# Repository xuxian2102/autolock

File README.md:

# HomeKey Lock Rev A — PN7161 / ESP32-C6

本工程是面向嘉立创 4 层 PCB + 单面 PCBA 的第一版工程样机，目标是：

1. iPhone / Apple Watch 通过真正的 Apple HomeKey 认证；
2. ESP32-C6 驱动 180° DS3115 舵机压下室内门把手并立即复位；
3. 3S 保护电池供电，USB-C 可单独给逻辑与 NFC 供电、刷机和调试；
4. 门外不增加可见器件，不接门磁、不集成 3S 充电器。

## Rev A 设计边界

- 主控：ESP32-C6-MINI-1-N4，4 MB Flash。
- NFC：PN7161B1HN/C100E，SPI，27.12 MHz 晶振。
- 天线：PCB 顶层 40 mm × 40 mm、4 匝、0.4 mm 线宽、0.3 mm 间距；匹配值按 NXP AN13219 Rev.1.6 的首次迭代值。
- 电池输入：9.0–12.6 V（3S 保护电池或 12 V/5 A 台式适配器）。
- 舵机输出：约 5.94 V，TPS565201 额定 5 A；仅在动作时使能。
- USB-C：USB 2.0 D+/D− 连接 ESP32-C6 原生 USB Serial/JTAG；USB VBUS 只能带逻辑/NFC，不能带舵机。
- USB 与电池逻辑 5 V 用两颗 B5819W 肖特基二极管合路，互不反灌；`SYS_5V` 会比来源低约 0.2–0.4 V。
- 板层：4 层、1.6 mm、1 oz；所有器件位于顶层，降低 PCBA 成本。
- 不含：电池充电、门状态检测、机械限位检测、认证固件、外壳与舵机连杆。

## 必须先知道

这是 Rev A RF/机构验证板。40 mm 天线的匹配值只是在空气中的起点；门板、锁体、螺丝、铁氧体片和安装胶都会改变天线的电感、Q 值和谐振。首批应下单 5 块裸板、2 块 PCBA，先在家中厚门完成读取距离、HomeKey 成功率、待机电流和舵机堵转测试，再决定 Rev B。

HomeKey-ESP32 对 PN7161 的支持仍属于开发/实验路径。硬件把 IRQ 放在 ESP32-C6 的低功耗 GPIO0，并保留 VEN、SPI 和调试测试点；低功耗轮询与深睡唤醒仍需在固件中验证。

## 从源码重建

工程是生成出来的，不是手工画的。`tools/design_data.py` 是元件与网表的唯一真源，
`tools/generate_board.py` 里的 `FIXED_PLACEMENT` 是板上位置的唯一真源。

```bash
.claude/hooks/session-start.sh          # 装 KiCad 10.0.6 与依赖（幂等）
python3 tools/generate_board.py         # 摆放 → hardware/kicad/*.kicad_pcb
python3 tools/route_board.py            # 布线 + 接地敷铜
python3 tools/build_release.py          # 审计 + 官方 Gerber 导出 + 打包
python3 .claude/skills/kicad-verify/scripts/verify_release.py --strict
```

最后一步刻意不依赖 `tools/` 自带的审计脚本 —— 那套脚本既生成发布件又给发布件盖章。

## 当前生产状态

PCB 电气/几何审计已通过，原 21 个 LCSC 缺口已全部关闭；生产放行仍为 **HOLD**，等待在嘉立创预览器中确认 Gerber 和 CPL 旋转，并完成首板 RF/机构测试。详见 `reports/REV_A_RELEASE_STATUS.md` 与 `hardware/production/JLCPCB_ORDER_NOTES.md`。

## 目录

```
autolock/
├── README.md
├── hardware/
│   ├── kicad/                    KiCad 源工程：原理图、PCB、符号/封装库、3D 模型
│   ├── docs/                     原理图总 PDF + 分页 PDF
│   └── production/
│       ├── gerbers/              13 个制造文件（11 层 Gerber X2 + PTH/NPTH Excellon），平铺
│       ├── gerber.zip            嘉立创上传用，内容与 gerbers/ 逐字节一致
│       ├── assembly/             BOM_FULL / BOM_JLCPCB_DRAFT / CPL_JLCPCB_DRAFT / PROCUREMENT_GAPS
│       ├── JLCPCB_ORDER_NOTES.md 下单参数与预览确认清单
│       └── CHECKSUMS.sha256      上述制造文件的 SHA-256 清单
├── design/                       Rev A 设计冻结说明与 U4 板级片段
├── firmware/                     固定引脚表（不打包第三方固件二进制）
├── tools/                        原理图/PCB 生成、布线、审计、生产导出和发布打包脚本
├── reports/                      最终审查记录 + 手机可看的分层渲染图
├── .claude/
│   ├── hooks/                    SessionStart：装 KiCad 10.0.6、补齐未声明的 Python 依赖、
│   │                             搭好 tools/ 期望的便携 KiCad 目录
│   └── skills/kicad-verify/      独立验证：DRC、网表逐焊盘对 design_data.py、
│                                 引脚图对数据手册、Gerber 逐字节复现
├── INDEPENDENT_REVIEW_KICAD10.md 用独立安装的 KiCad 10 做的首轮复核
├── PREFAB_REVIEW_ACTIONS.md      投产前优化点与修改点全表（含已完成项）
├── MODULE_REVIEW.md              分模块复核：电源、NFC、RF、舵机
└── FINAL_LOCAL_PRODUCTION_REVIEW.md
```

- `hardware/kicad/`：`.kicad_sch` 是权威原理图（见 `hardware/docs/SCHEMATIC_PDF_STATUS.md` 的 PDF 限制说明）。
- `hardware/production/`：直接用于下单的一套文件；`gerber.zip` 就是上传给嘉立创的那个包。
- `reports/`：布线、几何、物理连通、CPL 定位和生产导出的最终审计，以及官方逐层 PNG/SVG。
  构建过程中产生的中间态 DRC/同步快照已不再入库，只保留最终版记录。

## 安全边界

- 必须保留原机械钥匙和室内手动开门能力；任何故障不得把人困在室内。
- 只使用带 BMS 的 3S 电池包和与该电池匹配的认证充电器；Rev A 不允许直接给裸电芯充电。
- 舵机固件必须设置动作超时和看门狗；调试时先拆下舵机臂。
- 逆向实现的 HomeKey 固件不等同于 MFi 认证商业锁，不应作为高风险场所唯一安防手段。

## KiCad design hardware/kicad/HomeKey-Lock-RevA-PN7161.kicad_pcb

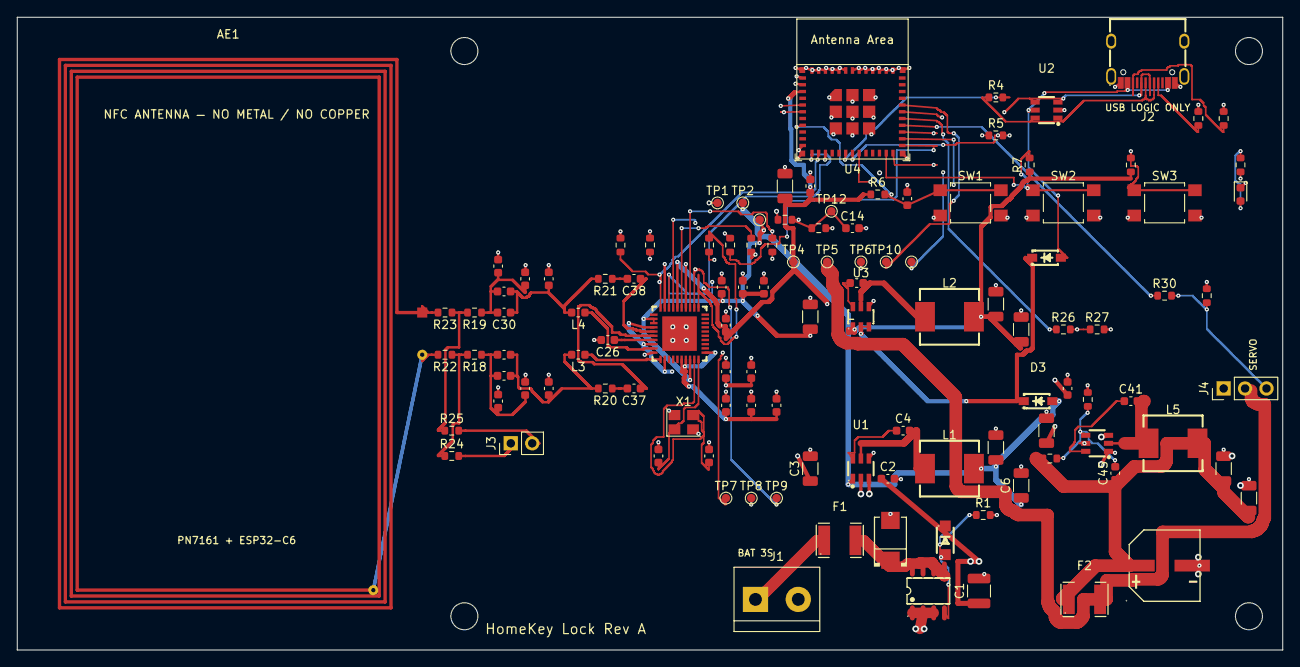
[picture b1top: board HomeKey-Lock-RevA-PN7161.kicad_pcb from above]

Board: 4 copper layers, 150.0 x 75.0 mm, 120 parts (0 on the bottom side), 68 nets.

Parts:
AE1: 40x65mm 4-turn PCB antenna; NFC_Antenna_40x65_4T
C1: 22uF 25V; C_1210_3225Metric
C2: 100nF 50V; C_0603_1608Metric_ValueHidden
C3: 10uF 25V; C_1206_3216Metric_ValueHidden
C4, C8, C14, C41: 100nF; C_0603_1608Metric
C5, C9, C10: 22uF 10V; C_1206_3216Metric_FabRef
C6: 22uF 10V; C_1206_3216Metric_ValueHidden
C7, C11: 10uF 10V; C_1206_3216Metric_FabRef
C12, C17, C23: 100nF; C_0603_1608Metric_FabRef
C13: 1uF; C_0603_1608Metric_FabRef
C15, C16: 10pF C0G; C_0603_1608Metric_FabRef
C18, C20: 4.7uF 10V; C_0603_1608Metric_FabRef
C19: 1uF 10V; C_0603_1608Metric_FabRef
C21, C22, C24, C25: 2.2uF 10V; C_0603_1608Metric_FabRef
C26: 100nF; C_0603_1608Metric_ValueHidden
C27, C28: 330pF C0G 2%; C_0603_1608Metric_FabRef
C29: 51pF NP0 1%; C_0603_1608Metric_FabRef
C30: 51pF NP0 1%; C_0603_1608Metric_ValueHidden
C31, C32: 75pF NP0 1%; C_0603_1608Metric_FabRef
C33, C34, C35, C36: DNP trim; C_0603_1608Metric_FabRef
C37, C38: 1nF C0G; C_0603_1608Metric_ValueHidden
C39: 10uF 25V; C_1206_3216Metric_FabRef
C40: 100nF 50V; C_0603_1608Metric_FabRef
C42, C43: 47uF 10V; C_1206_3216Metric_FabRef
C44: 1000uF 10V; CAP-SMD_BD8.0-L8.3-W8.3-FD
C45: 22pF DNP; C_0603_1608Metric_FabRef
D1: SMBJ15A; SMB_L4.6-W3.6-LS5.3-RD
D2: 10V Zener; SOD-123FL_L2.6-W1.6-LS3.5-R-FD
D3, D4: B5819W; SOD-123_L2.7-W1.6-LS3.7-RD-1
D5: Green LED; LED_0603_1608Metric
F1: 3A 30V PPTC; F1812
F2: 2.5A 16V PPTC; F1812
H1, H2, H3, H4: M3; MountingHole_3.2mm_M3
J1: BATTERY 3S 9.0-12.6V; TerminalBlock_1x02_P5.08mm
J2: USB-C USB2; USB-C_SMD-TYPE-C-31-M-12_1
J3: EXT ANT DNP; PinHeader_1x02_P2.54mm_Vertical
J4: DS3115 SERVO; PinHeader_1x03_P2.54mm_Vertical
L1, L2, L5: 4.7uH 6A; IND-SMD_L7.0-W6.6_APH0630
L3, L4: 160nH 5% RF; L_0603_1608Metric
Q1: AO4407A; SOIC-8_L4.9-W3.9-P1.27-LS6.0-BL
R1, R27: 100k; R_0603_1608Metric
R2, R3: 5.1k; R_0603_1608Metric_FabRef
R4, R5: 22R; R_0603_1608Metric
R6, R26: 10k; R_0603_1608Metric
R7: 10k; R_0603_1608Metric_ValueHidden
R8, R12, R31: 10k; R_0603_1608Metric_FabRef
R9: 100R; R_0603_1608Metric_FabRef
R10: 1M; R_0603_1608Metric
R11: 220k; R_0603_1608Metric
R13: 100k; R_0603_1608Metric_FabRef
R14, R15, R16, R17: 0R; R_0603_1608Metric_FabRef
R18, R19: 2.7R 1%; R_0603_1608Metric_ValueHidden
R20, R21: 2.2k 1%; R_0603_1608Metric_ValueHidden
R22, R23: 0R ANT ON; R_0603_1608Metric_ValueHidden
R24, R25: DNP EXT; R_0603_1608Metric
R28: 68.1k 1%; R_0603_1608Metric_FabRef
R29: 10k 1%; R_0603_1608Metric_FabRef
R30: 220R; R_0603_1608Metric
SW1: RESET; SW_SPST_TL3305A
SW2: BOOT; SW_SPST_TL3305A
SW3: SERVICE; SW_SPST_TL3305A
TP1: BAT_SYS; TestPoint_Pad_D1.0mm
TP2: 5V_BAT; TestPoint_Pad_D1.0mm
TP3: SYS_5V; TestPoint_Pad_D1.0mm
TP4: 3V3; TestPoint_Pad_D1.0mm
TP5: SERVO_6V_OUT; TestPoint_Pad_D1.0mm
TP6: GND; TestPoint_Pad_D1.0mm
TP7: PN_IRQ; TestPoint_Pad_D1.0mm
TP8: PN_VEN; TestPoint_Pad_D1.0mm
TP9: PN_DWL_REQ; TestPoint_Pad_D1.0mm
TP10: UART_TX; TestPoint_Pad_D1.0mm
TP11: UART_RX; TestPoint_Pad_D1.0mm
TP12: BAT_ADC; TestPoint_Pad_D1.0mm
U1: AP63205WU-7 5V; TSOT-23-6_L2.9-W1.6-P0.95-LS2.8-BL
U2: USBLC6-2SC6; SOT-23-6_L2.9-W1.6-P0.95-LS2.8-BR
U3: AP63203WU-7 3V3; TSOT-26_L2.9-W1.6-P0.95-LS2.8-BL
U4: ESP32-C6-MINI-1-N4; ESP32-C6-MINI-1
U5: PN7161B1HN/C100E; HVQFN-40_L6.0-W6.0-P0.50-BL-EP4.1
U6: TPS565201DDCR; SOT-23-6_L2.9-W1.6-P0.95-LS2.8-BR
X1: 27.12MHz 10pF; Crystal_SMD_3225-4Pin_3.2x2.5mm

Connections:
3V3: C9.1, C10.1, C11.1, C12.1, C19.1, L2.2, R6.1, R7.1, R8.1, TP4.1, U3.1, U4.3, U5.6
5V_BAT: C5.1, C6.1, D3.2, L1.2, TP2.1, U1.1
ANT_N: AE1.1, R23.2
ANT_P: AE1.2, R22.2
BAT_ADC: C14.1, R10.2, R11.1, TP12.1, U4.5
BAT_FUSED: D1.1, F1.2, Q1.5, Q1.6, Q1.7, Q1.8
BAT_RAW: F1.1, J1.1
BAT_SYS: C1.1, C2.1, C3.1, C39.1, C40.1, D2.1, Q1.1, Q1.2, Q1.3, R10.1, TP1.1, U1.2, U1.3, U6.3
BOOT: R7.2, SW2.1, U4.23
BST_3V3: C8.1, U3.6
BST_5V: C4.1, U1.6
BST_SERVO: C41.1, U6.6
ESP_EN: C13.1, R6.2, SW1.1, U4.8
EXT_ANT_N: J3.2, R25.2
EXT_ANT_P: J3.1, R24.2
GND: C1.2, C2.2, C3.2, C5.2, C6.2, C7.2, C9.2, C10.2, C11.2, C12.2, C13.2, C14.2, C15.2, C16.2, C17.2, C18.2, C19.2, C20.2, C21.2, C22.2, C23.2, C24.2, C25.2, C26.2, C27.2, C28.2, C31.2, C32.2, C35.2, C36.2, C39.2, C40.2, C42.2, C43.2, C44.2, D1.2, D5.1, J1.2, J2.1, J2.2, J2.3, J2.4, J2.A1B12, J2.B1A12, J4.1, R1.2, R2.2, R3.2, R11.2, R12.2, R13.2, R27.2, R29.2, R31.2, SW1.2, SW2.2, SW3.2, TP6.1, U1.4, U2.2, U3.4, U4.1, U4.2, U4.11, U4.14, U4.36, U4.37, U4.38, U4.39, U4.40, U4.41, U4.42, U4.43, U4.44, U4.45, U4.46, U4.47, U4.48, U4.49, U4.50, U4.51, U4.52, U4.53, U5.4, U5.9, U5.20, U5.41, U6.1, X1.2, X1.4
LED_A: D5.2, R9.2
PMOS_GATE: D2.2, Q1.4, R1.1
PN_DWL_REQ: R12.1, TP9.1, U5.2
PN_IRQ: TP7.1, U4.12, U5.8
PN_MISO: R17.1, U4.27
PN_MISO_IC: R17.2, U5.5
PN_MOSI: R16.1, U4.26
PN_MOSI_IC: R16.2, U5.3
PN_NSS: R14.1, U4.24
PN_NSS_IC: R14.2, U5.1
PN_RXN: C38.1, U5.15
PN_RXP: C37.1, U5.16
PN_SCK: R15.1, U4.25
PN_SCK_IC: R15.2, U5.7
PN_TVDD: C21.1, C22.1, U5.14, U5.18, U5.22
PN_TX1: L3.1, U5.21
PN_TX2: L4.1, U5.19
PN_VDD: C23.1, C24.1, C25.1, U5.26, U5.27, U5.31
PN_VEN: R13.1, TP8.1, U4.13, U5.10
PN_VMID: C26.1, U5.17
RF_N0: C28.1, C30.1, C34.1, L4.2, R21.2
RF_N1: C30.2, C32.1, C34.2, C36.1, R19.1
RF_N2: R19.2, R23.1, R25.1
RF_P0: C27.1, C29.1, C33.1, L3.2, R20.2
RF_P1: C29.2, C31.1, C33.2, C35.1, R18.1
RF_P2: R18.2, R22.1, R24.1
RXN_AC: C38.2, R21.1
RXP_AC: C37.2, R20.1
SERVICE_BTN: R8.2, SW3.1, U4.6
SERVO_6V: C42.1, C43.1, C44.1, C45.1, F2.1, L5.2, R28.1
SERVO_6V_OUT: F2.2, J4.2, TP5.1
SERVO_EN: R26.1, U4.29
SERVO_EN_IC: R26.2, R27.1, U6.5
SERVO_FB: C45.2, R28.2, R29.1, U6.4
SERVO_PWM: R30.1, U4.28
SERVO_PWM_OUT: J4.3, R30.2, R31.1
STATUS_LED: R9.1, U4.19
SW_3V3: C8.2, L2.1, U3.5
SW_5V: C4.2, L1.1, U1.5
SW_SERVO: C41.2, L5.1, U6.2
SYS_5V: C7.1, C17.1, C18.1, C20.1, D3.1, D4.1, TP3.1, U3.2, U3.3, U5.12, U5.13, U5.28
UART_RX: TP11.1, U4.30
UART_TX: TP10.1, U4.31
USB_5V: D4.2, J2.A4B9, J2.B4A9, U2.5
USB_CC1: J2.A5, R2.1
USB_CC2: J2.B5, R3.1
USB_DM: R4.2, U4.17
USB_DN_CONN: J2.A7, J2.B7, R4.1, U2.1, U2.6
USB_DP: R5.2, U4.18
USB_DP_CONN: J2.A6, J2.B6, R5.1, U2.3, U2.4
XTAL1: C15.1, U5.30, X1.1
XTAL2: C16.1, U5.29, X1.3

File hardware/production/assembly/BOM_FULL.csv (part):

Designator,Value,Footprint,LCSC,MPN,Manufacturer,Status,Assembly,Note
J1,BATTERY 3S 9.0-12.6V,HomeKey_RevA:TerminalBlock_1x02_P5.08mm,C8465,,,READY,MANUAL_THT,5.08 mm screw terminal; verify THT assembly option
F1,3A 30V PPTC,HomeKey_RevA:F1812,C47002391,SMD1812-300C-30V,BNstar,READY,SMT,
D1,SMBJ15A,HomeKey_RevA:SMB_L4.6-W3.6-LS5.3-RD,C320232,SMBJ15A,,READY,SMT,
Q1,AO4407A,HomeKey_RevA:SOIC-8_L4.9-W3.9-P1.27-LS6.0-BL,C16072,AO4407A,AOS,READY,SMT,
R1,100k,HomeKey_RevA:R_0603_1608Metric,C25803,,UNI-ROYAL,READY,SMT,
D2,10V Zener,HomeKey_RevA:SOD-123FL_L2.6-W1.6-LS3.5-R-FD,C209597,KDZVTR10B,,READY,SMT,
C1,22uF 25V,HomeKey_RevA:C_1210_3225Metric,C515687,,,READY,SMT,
C2,100nF 50V,HomeKey_RevA:C_0603_1608Metric_ValueHidden,C1591,,,READY,SMT,
U1,AP63205WU-7 5V,HomeKey_RevA:TSOT-23-6_L2.9-W1.6-P0.95-LS2.8-BL,C2071056,AP63205WU-7,Diodes Inc.,READY,SMT,
C3,10uF 25V,HomeKey_RevA:C_1206_3216Metric_ValueHidden,C9807,CL31A106KAHNNNE,Samsung Electro-Mechanics,READY,SMT,
C4,100nF,HomeKey_RevA:C_0603_1608Metric,C1591,,,READY,SMT,
L1,4.7uH 6A,HomeKey_RevA:IND-SMD_L7.0-W6.6_APH0630,C5349705,APH0630T4R7M,,READY,SMT,
C5,22uF 10V,HomeKey_RevA:C_1206_3216Metric_FabRef,C5672,,,READY,SMT,
C6,22uF 10V,HomeKey_RevA:C_1206_3216Metric_ValueHidden,C5672,,,READY,SMT,
D3,B5819W,HomeKey_RevA:SOD-123_L2.7-W1.6-LS3.7-RD-1,C8598,B5819W,,READY,SMT,
J2,USB-C USB2,HomeKey_RevA:USB-C_SMD-TYPE-C-31-M-12_1,C165948,TYPE-C-31-M-12,HRO,READY,SMT,
R2,5.1k,HomeKey_RevA:R_0603_1608Metric_FabRef,C2907044,,UNI-ROYAL,READY,SMT,
R3,5.1k,HomeKey_RevA:R_0603_1608Metric_FabRef,C2907044,,UNI-ROYAL,READY,SMT,
U2,USBLC6-2SC6,HomeKey_RevA:SOT-23-6_L2.9-W1.6-P0.95-LS2.8-BR,C5261088,USBLC6-2SC6,,READY,SMT,
R4,22R,HomeKey_RevA:R_0603_1608Metric,C23345,0603WAF220JT5E,UNI-ROYAL,READY,SMT,
R5,22R,HomeKey_RevA:R_0603_1608Metric,C23345,0603WAF220JT5E,UNI-ROYAL,READY,SMT,
D4,B5819W,HomeKey_RevA:SOD-123_L2.7-W1.6-LS3.7-RD-1,C8598,B5819W,,READY,SMT,
U3,AP63203WU-7 3V3,HomeKey_RevA:TSOT-26_L2.9-W1.6-P0.95-LS2.8-BL,C780769,AP63203WU-7,Diodes Inc.,READY,SMT,
C7,10uF 10V,HomeKey_RevA:C_1206_3216Metric_FabRef,C9807,CL31A106KAHNNNE,Samsung Electro-Mechanics,READY,SMT,
C8,100nF,HomeKey_RevA:C_0603_1608Metric,C1591,,,READY,SMT,
L2,4.7uH 6A,HomeKey_RevA:IND-SMD_L7.0-W6.6_APH0630,C5349705,APH0630T4R7M,,READY,SMT,
C9,22uF 10V,HomeKey_RevA:C_1206_3216Metric_FabRef,C5672,,,READY,SMT,
C10,22uF 10V,HomeKey_RevA:C_1206_3216Metric_FabRef,C5672,,,READY,SMT,
U4,ESP32-C6-MINI-1-N4,HomeKey_RevA:ESP32-C6-MINI-1,C5736265,ESP32-C6-MINI-1-N4,Espressif,READY,SMT,
C11,10uF 10V,HomeKey_RevA:C_1206_3216Metric_FabRef,C9807,CL31A106KAHNNNE,Samsung Electro-Mechanics,READY,SMT,
C12,100nF,HomeKey_RevA:C_0603_1608Metric_FabRef,C1591,,,READY,SMT,
R6,10k,HomeKey_RevA:R_0603_1608Metric,C25804,,UNI-ROYAL,READY,SMT,
C13,1uF,HomeKey_RevA:C_0603_1608Metric_FabRef,C15849,,,READY,SMT,
SW1,RESET,HomeKey_RevA:SW_SPST_TL3305A,C2886899,TL3305AF160QG,E-Switch,READY,SMT,
R7,10k,HomeKey_RevA:R_0603_1608Metric_ValueHidden,C25804,,UNI-ROYAL,READY,SMT,
SW2,BOOT,HomeKey_RevA:SW_SPST_TL3305A,C2886899,TL3305AF160QG,E-Switch,READY,SMT,
R8,10k,HomeKey_RevA:R_0603_1608Metric_FabRef,C25804,,UNI-ROYAL,READY,SMT,
SW3,SERVICE,HomeKey_RevA:SW_SPST_TL3305A,C2886899,TL3305AF160QG,E-Switch,READY,SMT,
D5,Green LED,HomeKey_RevA:LED_0603_1608Metric,C12624,KT-0603G,Hubei KENTO Elec,READY,SMT,"Verified standard polarity: pin 1=K to GND, pin 2=A to R9; rotate footprint 180 degrees in place"
R9,100R,HomeKey_RevA:R_0603_1608Metric_FabRef,C22775,0603WAF1000T5E,UNI-ROYAL,READY,SMT,
R10,1M,HomeKey_RevA:R_0603_1608Metric,C105578,,UNI-ROYAL,READY,SMT,
R11,220k,HomeKey_RevA:R_0603_1608Metric,C22961,0603WAF2203T5E,UNI-ROYAL,READY,SMT,
C14,100nF,HomeKey_RevA:C_0603_1608Metric,C1591,,,READY,SMT,
U5,PN7161B1HN/C100E,HomeKey_RevA:HVQFN-40_L6.0-W6.0-P0.50-BL-EP4.1,C3303780,PN7161B1HN/C100E,NXP,READY,SMT,"Pins 11,23-25,32-40 NC; DCDC_EN is an output and is intentionally NC"
X1,27.12MHz 10pF,HomeKey_RevA:Crystal_SMD_3225-4Pin_3.2x2.5mm,C90919,7M27100009,TXC,READY,SMT,
C15,10pF C0G,HomeKey_RevA:C_0603_1608Metric_FabRef,C1634,,,READY,SMT,
C16,10pF C0G,HomeKey_RevA:C_0603_1608Metric_FabRef,C1634,,,READY,SMT,
R12,10k,HomeKey_RevA:R_0603_1608Metric_FabRef,C25804,,UNI-ROYAL,READY,SMT,
R13,100k,HomeKey_RevA:R_0603_1608Metric_FabRef,C25803,,UNI-ROYAL,READY,SMT,
R14,0R,HomeKey_RevA:R_0603_1608Metric_FabRef,C21189,,UNI-ROYAL,READY,SMT,
R15,0R,HomeKey_RevA:R_0603_1608Metric_FabRef,C21189,,UNI-ROYAL,READY,SMT,
R16,0R,HomeKey_RevA:R_0603_1608Metric_FabRef,C21189,,UNI-ROYAL,READY,SMT,
R17,0R,HomeKey_RevA:R_0603_1608Metric_FabRef,C21189,,UNI-ROYAL,READY,SMT,
C17,100nF,HomeKey_RevA:C_0603_1608Metric_FabRef,C1591,,,READY,SMT,
C18,4.7uF 10V,HomeKey_RevA:C_0603_1608Metric_FabRef,C1705,,,READY,SMT,
C19,1uF 10V,HomeKey_RevA:C_0603_1608Metric_FabRef,C15849,,,READY,SMT,
C20,4.7uF 10V,HomeKey_RevA:C_0603_1608Metric_FabRef,C1705,,,READY,SMT,
C21,2.2uF 10V,HomeKey_RevA:C_0603_1608Metric_FabRef,C1607,,,READY,SMT,
C22,2.2uF 10V,HomeKey_RevA:C_0603_1608Metric_FabRef,C1607,,,READY,SMT,
C23,100nF,HomeKey_RevA:C_0603_1608Metric_FabRef,C1591,,,READY,SMT,
C24,2.2uF 10V,HomeKey_RevA:C_0603_1608Metric_FabRef,C1607,,,READY,SMT,
C25,2.2uF 10V,HomeKey_RevA:C_0603_1608Metric_FabRef,C1607,,,READY,SMT,
C26,100nF,HomeKey_RevA:C_0603_1608Metric_ValueHidden,C1591,,,READY,SMT,
L3,160nH 5% RF,HomeKey_RevA:L_0603_1608Metric,C437367,LQW18CNR16J00D,,READY,SMT,
L4,160nH 5% RF,HomeKey_RevA:L_0603_1608Metric,C437367,LQW18CNR16J00D,,READY,SMT,
C27,330pF C0G 2%,HomeKey_RevA:C_0603_1608Metric_FabRef,C882521,GRM1885C1H331FA01D,Murata Electronics,READY,SMT,
C28,330pF C0G 2%,HomeKey_RevA:C_0603_1608Metric_FabRef,C882521,GRM1885C1H331FA01D,Murata Electronics,READY,SMT,
C29,51pF NP0 1%,HomeKey_RevA:C_0603_1608Metric_FabRef,C519494,CC0603FRNPO9BN510,YAGEO,READY,SMT,
C30,51pF NP0 1%,HomeKey_RevA:C_0603_1608Metric_ValueHidden,C519494,CC0603FRNPO9BN510,YAGEO,READY,SMT,
C31,75pF NP0 1%,HomeKey_RevA:C_0603_1608Metric_FabRef,C519496,CC0603FRNPO9BN750,YAGEO,READY,SMT,
C32,75pF NP0 1%,HomeKey_RevA:C_0603_1608Metric_FabRef,C519496,CC0603FRNPO9BN750,YAGEO,READY,SMT,
C33,DNP trim,HomeKey_RevA:C_0603_1608Metric_FabRef,,,,DNP,SMT,
C34,DNP trim,HomeKey_RevA:C_0603_1608Metric_FabRef,,,,DNP,SMT,
C35,DNP trim,HomeKey_RevA:C_0603_1608Metric_FabRef,,,,DNP,SMT,
C36,DNP trim,HomeKey_RevA:C_0603_1608Metric_FabRef,,,,DNP,SMT,
C37,1nF C0G,HomeKey_RevA:C_0603_1608Metric_ValueHidden,C163508,,,READY,SMT,
C38,1nF C0G,HomeKey_RevA:C_0603_1608Metric_ValueHidden,C163508,,,READY,SMT,
R18,2.7R 1%,HomeKey_RevA:R_0603_1608Metric_ValueHidden,C22946,0603WAF270KT5E,UNI-ROYAL,READY,SMT,
R19,2.7R 1%,HomeKey_RevA:R_0603_1608Metric_ValueHidden,C22946,0603WAF270KT5E,UNI-ROYAL,READY,SMT,
R20,2.2k 1%,HomeKey_RevA:R_0603_1608Metric_ValueHidden,C4190,0603WAF2201T5E,UNI-ROYAL,READY,SMT,
R21,2.2k 1%,HomeKey_RevA:R_0603_1608Metric_ValueHidden,C4190,0603WAF2201T5E,UNI-ROYAL,READY,SMT,
R22,0R ANT ON,HomeKey_RevA:R_0603_1608Metric_ValueHidden,C21189,,UNI-ROYAL,READY,SMT,
R23,0R ANT ON,HomeKey_RevA:R_0603_1608Metric_ValueHidden,C21189,,UNI-ROYAL,READY,SMT,
R24,DNP EXT,HomeKey_RevA:R_0603_1608Metric,C21189,,UNI-ROYAL,DNP,SMT,
R25,DNP EXT,HomeKey_RevA:R_0603_1608Metric,C21189,,UNI-ROYAL,DNP,SMT,
J3,EXT ANT DNP,HomeKey_RevA:PinHeader_1x02_P2.54mm_Vertical,,,,DNP,MANUAL_THT,Unpopulated fallback pads; never fit at the same time as R22/R23 without retuning
AE1,40x65mm 4-turn PCB antenna,HomeKey_RevA:NFC_Antenna_40x65_4T,,,,BOARD_COPPER,SMT,Board-defined copper; excluded from BOM and placement
U6,TPS565201DDCR,HomeKey_RevA:SOT-23-6_L2.9-W1.6-P0.95-LS2.8-BR,C327676,TPS565201DDCR,Texas Instruments,READY,SMT,
C39,10uF 25V,HomeKey_RevA:C_1206_3216Metric_FabRef,C9807,CL31A106KAHNNNE,Samsung Electro-Mechanics,READY,SMT,
C40,100nF 50V,HomeKey_RevA:C_0603_1608Metric_FabRef,C1591,,,READY,SMT,
R26,10k,HomeKey_RevA:R_0603_1608Metric,C25804,,UNI-ROYAL,READY,SMT,
R27,100k,HomeKey_RevA:R_0603_1608Metric,C25803,,UNI-ROYAL,READY,SMT,
C41,100nF,HomeKey_RevA:C_0603_1608Metric,C1591,,,READY,SMT,
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
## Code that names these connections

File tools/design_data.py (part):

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# Page 2: ESP32-C6, user controls and sensing
# ---------------------------------------------------------------------------
esp_pins = {str(n): "GND" for n in [1, 2, 11, 14, *range(36, 54)]}
esp_pins.update({"3": "3V3", "5": "BAT_ADC", "6": "SERVICE_BTN", "8": "ESP_EN",
                 "12": "PN_IRQ", "13": "PN_VEN", "17": "USB_DM", "18": "USB_DP",
                 "19": "STATUS_LED", "23": "BOOT", "24": "PN_NSS", "25": "PN_SCK",
                 "26": "PN_MOSI", "27": "PN_MISO", "28": "SERVO_PWM", "29": "SERVO_EN",
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# ---------------------------------------------------------------------------
# Page 3: PN7161 controller and its local supplies/clock
# ---------------------------------------------------------------------------
pn_pins = {"1": "PN_NSS", "2": "PN_DWL_REQ", "3": "PN_MOSI", "4": "GND", "5": "PN_MISO",
           "6": "3V3", "7": "PN_SCK", "8": "PN_IRQ", "9": "GND", "10": "PN_VEN",
           "12": "SYS_5V", "13": "SYS_5V", "14": "PN_TVDD", "15": "PN_RXN", "16": "PN_RXP",
           "17": "PN_VMID", "18": "PN_TVDD", "19": "PN_TX2", "20": "GND", "21": "PN_TX1",
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for i, net in enumerate(["PN_NSS", "PN_SCK", "PN_MOSI", "PN_MISO"], start=14):
    resistor(f"R{i}", "0R", {"1": net, "2": net + "_IC"}, "03_NFC_CONTROLLER", "Host interface", (53 + (i-14)*2.5, 29, 90), lcsc="C21189")
# Correct the IC-side pin nets after the series resistors.
pn_pins["1"] = "PN_NSS_IC"; pn_pins["7"] = "PN_SCK_IC"; pn_pins["3"] = "PN_MOSI_IC"; pn_pins["5"] = "PN_MISO_IC"
next(p for p in parts if p.ref == "U5").pins.update(pn_pins)

capacitor("C17", "100nF", {"1": "SYS_5V", "2": "GND"}, "03_NFC_CONTROLLER", "PN7161 supply", (66, 34, 90), lcsc="C1591")
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capacitor("C36", "DNP trim", {"1": "RF_N1", "2": "GND"}, "04_RF_ANTENNA", "Matching", (42, 43, 90), dnp=True)
capacitor("C37", "1nF C0G", {"1": "PN_RXP", "2": "RXP_AC"}, "04_RF_ANTENNA", "Receiver tap", (57, 31, 0), lcsc="C163508")
capacitor("C38", "1nF C0G", {"1": "PN_RXN", "2": "RXN_AC"}, "04_RF_ANTENNA", "Receiver tap", (57, 44, 0), lcsc="C163508")
resistor("R18", "2.7R 1%", {"1": "RF_P1", "2": "RF_P2"}, "04_RF_ANTENNA", "Q damping", (43, 35.5, 0),
         lcsc="C22946", mpn="0603WAF270KT5E")
resistor("R19", "2.7R 1%", {"1": "RF_N1", "2": "RF_N2"}, "04_RF_ANTENNA", "Q damping", (43, 38.5, 0),
         lcsc="C22946", mpn="0603WAF270KT5E")
resistor("R20", "2.2k 1%", {"1": "RXP_AC", "2": "RF_P0"}, "04_RF_ANTENNA", "Receiver tap", (53, 31, 0),
         lcsc="C4190", mpn="0603WAF2201T5E")
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def validate_manifest():
    refs = [p.ref for p in parts]
    assert len(refs) == len(set(refs)), "duplicate reference designator"
    assert part_by_ref("U5").pins["1"] == "PN_NSS_IC"
    assert part_by_ref("U4").pins["12"] == "PN_IRQ"
    assert part_by_ref("J4").pins == {"1": "GND", "2": "SERVO_6V_OUT", "3": "SERVO_PWM_OUT"}


validate_manifest()
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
